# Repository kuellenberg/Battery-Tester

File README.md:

# Battery-Tester
Simple resistive dummy load for battery lifetime tests

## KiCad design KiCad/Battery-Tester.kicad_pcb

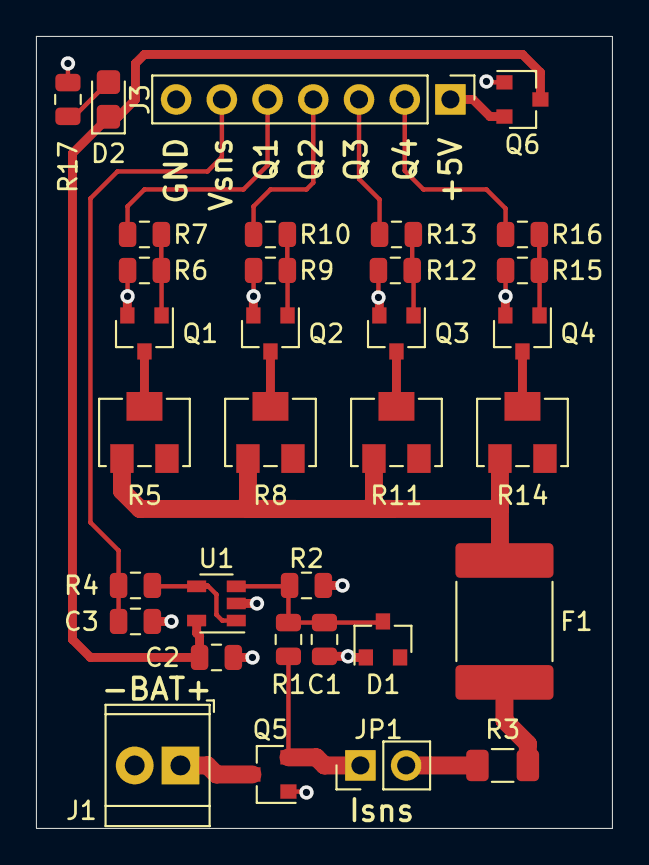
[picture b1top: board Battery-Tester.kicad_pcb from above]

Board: 2 copper layers, 32.0 x 44.0 mm, 33 parts (0 on the bottom side), 24 nets.

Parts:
C1, C2, C3: 100nF; C_0805_2012Metric
D1: 5V2; D_SOT-23_ANK
D2: LED; LED_0805_2012Metric_Castellated
F1: Polyfuse; Fuse_2920_7451Metric
J1: Conn_01x02; TerminalBlock_TE_282834-2_1x02_P2.54mm_Horizontal
J3: Conn_01x07; PinHeader_1x07_P2.54mm_Vertical
JP1: Jumper; PinHeader_1x02_P2.54mm_Vertical
Q1, Q2, Q3, Q4: SI2304DDS; SOT-23
Q5, Q6: Si2347DS; SOT-23
R1, R2: 1M, 0.1%; R_0805_2012Metric
R3: 10; R_1206_3216Metric
R4, R7, R10, R13, R16: 100; R_0805_2012Metric
R5, R8, R11: RTRIM; Potentiometer_Bourns_3224W_Vertical
R6, R9, R12, R15: 100k; R_0805_2012Metric
R14: 3224W-1-205G; Potentiometer_Bourns_3224W_Vertical
R17: 220; R_0805_2012Metric
U1: MCP6001-OT; SOT-23-5

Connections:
+5V: C2.1, D2.1, Q6.3, U1.5
GND: C1.2, C2.2, C3.2, D1.2, J1.2, J3.7, Q1.2, Q2.2, Q3.2, Q4.2, Q5.1, Q6.1, R2.1, R6.2, R9.2, R12.2, R15.2, R17.2, U1.2
unnamed: C1.1, D1.1, R1.1, R2.2, U1.3
unnamed: C3.1, J3.6, R4.2
unnamed: D2.2, R17.1
unnamed: F1.1, R3.2
unnamed: F1.2, R5.1, R8.1, R11.1, R14.1
unnamed: J1.1, Q5.3
unnamed: J3.1, Q6.2
unnamed: J3.2, R16.2
unnamed: J3.3, R13.2
unnamed: J3.4, R10.2
unnamed: J3.5, R7.2
unnamed: JP1.1, Q5.2, R1.2
unnamed: JP1.2, R3.1
unnamed: Q1.1, R6.1, R7.1
unnamed: Q1.3, R5.2
unnamed: Q2.1, R9.1, R10.1
unnamed: Q2.3, R8.2
unnamed: Q3.1, R12.1, R13.1
unnamed: Q3.3, R11.2
unnamed: Q4.1, R15.1, R16.1
unnamed: Q4.3, R14.2
unnamed: R4.1, U1.1, U1.4

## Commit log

2019-08-19 Minor modifications.
